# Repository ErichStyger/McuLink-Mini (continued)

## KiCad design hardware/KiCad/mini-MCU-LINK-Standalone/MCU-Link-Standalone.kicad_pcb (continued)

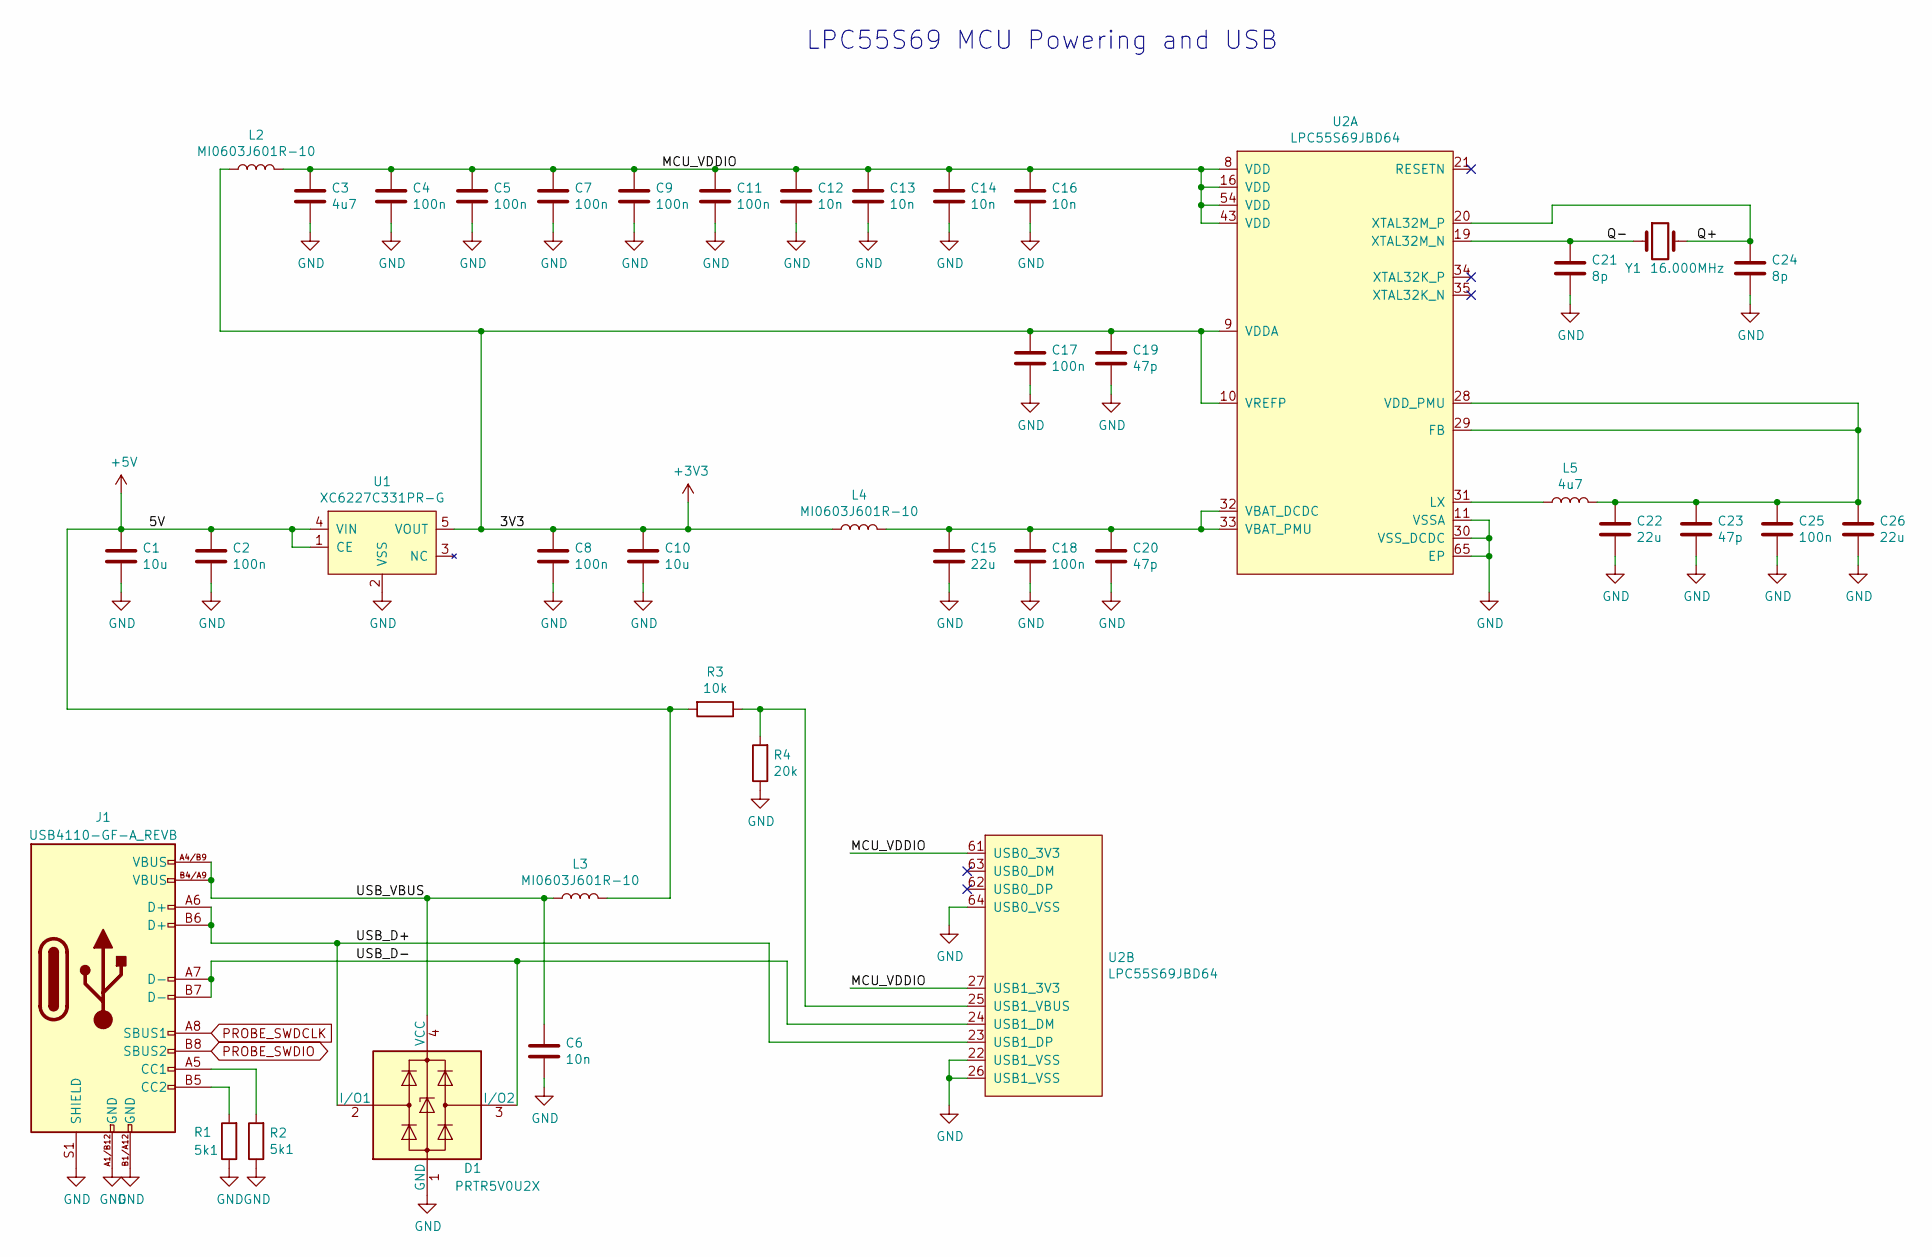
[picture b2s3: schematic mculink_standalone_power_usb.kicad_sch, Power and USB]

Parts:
C1, C10: 10u; C_0402_1005Metric
C2, C4, C5, C7, C8, C9, C11, C17, C18, C25: 100n; C_0402_1005Metric
C3: 4u7; C_0402_1005Metric
C6, C12, C13, C14, C16: 10n; C_0402_1005Metric
C15, C22, C26: 22u; C_0402_1005Metric
C19, C20, C23: 47p; C_0402_1005Metric
C21, C24: 8p; C_0402_1005Metric
D1: PRTR5V0U2X; SOT143B
J1: USB4110-GF-A_REVB; USB_C_Receptacle_GCT_USB4110-GF-A; PARTREV B
L2, L3, L4: MI0603J601R-10; L_0603_1608Metric
L5: 4u7; L_0603_1608Metric
R1, R2: 5k1; R_0402_1005Metric
R3: 10k; R_0402_1005Metric
R4: 20k; R_0402_1005Metric
U1: XC6227C331PR-G; SOT-89-5
U2: LPC55S69JBD64; LQFP-64-1EP_10x10mm_P0.5mm_EP5x5mm
Y1: 16.000MHz; CX3225GA16000D0PTVCC

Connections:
+3V3: C8.1, C10.1, C17.1, C19.1, L2.1, L4.1, U1.5 (VOUT), U2.9 (VDDA), U2.10 (VREFP); also elsewhere on the board
+5V: C1.1, C2.1, L3.2, R3.2, U1.1 (CE), U1.4 (VIN); also elsewhere on the board
/MCU-LINK Power and USB/MCU_VDDIO: C3.1, C4.1, C5.1, C7.1, C9.1, C11.1, C12.1, C13.1, C14.1, C16.1, L2.2, U2.8 (VDD), U2.16 (VDD), U2.27 (USB1_3V3), U2.43 (VDD), U2.54 (VDD), U2.61 (USB0_3V3)
/MCU-LINK Power and USB/Q+: C24.1, U2.20 (XTAL32M_P), Y1.2
/MCU-LINK Power and USB/Q-: C21.1, U2.19 (XTAL32M_N), Y1.1
/MCU-LINK Power and USB/USB_D+: D1.2 (I/O1), J1.A6 (D+), J1.B6 (D+), U2.23 (USB1_DP)
/MCU-LINK Power and USB/USB_D-: D1.3 (I/O2), J1.A7 (D-), J1.B7 (D-), U2.24 (USB1_DM)
/MCU-LINK Power and USB/USB_VBUS: C6.1, D1.4 (VCC), J1.A4/B9 (VBUS), J1.B4/A9 (VBUS), L3.1
GND: C1.2, C2.2, C3.2, C4.2, C5.2, C6.2, C7.2, C8.2, C9.2, C10.2, C11.2, C12.2, C13.2, C14.2, C15.2, C16.2, C17.2, C18.2, C19.2, C20.2, C21.2, C22.2, C23.2, C24.2, C25.2, C26.2, D1.1 (GND), J1.A1/B12 (GND), J1.B1/A12 (GND), J1.S1 (SHIELD), R1.1, R2.1, R4.1, U1.2 (VSS), U2.11 (VSSA), U2.22 (USB1_VSS), U2.26 (USB1_VSS), U2.30 (VSS_DCDC), U2.64 (USB0_VSS), U2.65 (EP); also elsewhere on the board
unnamed: J1.A5 (CC1), R2.2
unnamed: J1.B5 (CC2), R1.2
unnamed: C22.1, C23.1, C25.1, C26.1, L5.2, U2.28 (VDD_PMU), U2.29 (FB)
unnamed: L5.1, U2.31 (LX)
unnamed: C15.1, C18.1, C20.1, L4.2, U2.32 (VBAT_DCDC), U2.33 (VBAT_PMU)
unnamed: R3.1, R4.2, U2.25 (USB1_VBUS)
PROBE_SWDCLK: J1.A8 (SBUS1); also elsewhere on the board
PROBE_SWDIO: J1.B8 (SBUS2); also elsewhere on the board

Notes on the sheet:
LPC55S69 MCU Powering and USB

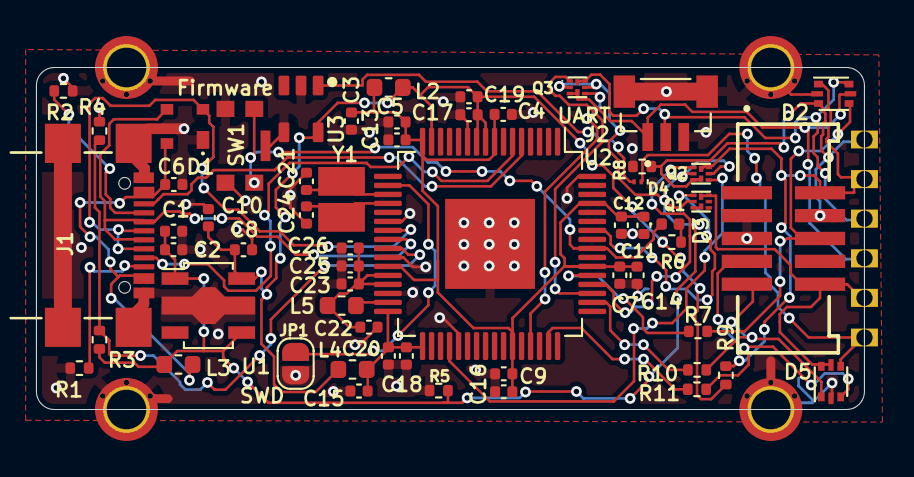
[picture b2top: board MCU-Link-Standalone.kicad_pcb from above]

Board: 2 copper layers, 46.0 x 19.0 mm, 69 parts (1 on the bottom side), 38 nets.

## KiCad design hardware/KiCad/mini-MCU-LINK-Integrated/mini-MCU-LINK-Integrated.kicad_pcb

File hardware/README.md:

# Outline
This folder contains hardware releated files and folders:
- Gerber: production files
- KiCad: KiCad project files for the standalone, intergrated and component version of the PCB

# Errata Rev v2.1
following resistors need to be removed
- R7, R6, R9 (100 Ohm resistor for UART Rx, Tx and SWCLK)

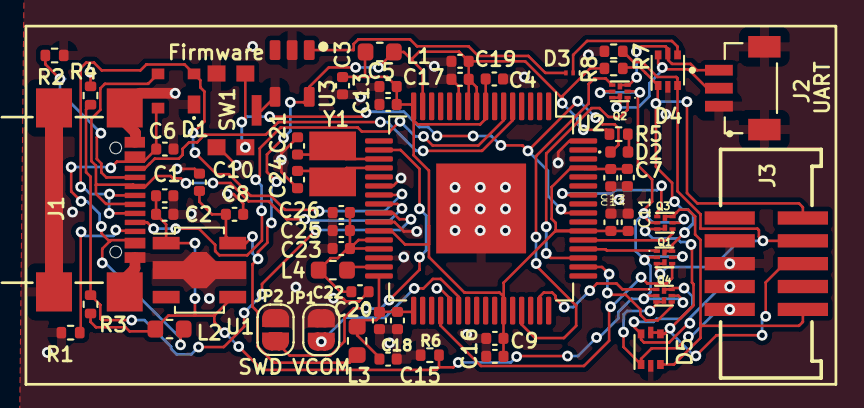
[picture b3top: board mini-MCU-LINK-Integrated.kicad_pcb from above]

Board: 2 copper layers, 57 parts (0 on the bottom side), 39 nets.

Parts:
C1, C10: 10u; C_0402_1005Metric
C2, C4, C5, C7, C8, C9, C11, C17, C18, C25: 100n; C_0402_1005Metric
C3: 4u7; C_0402_1005Metric
C6, C12, C13, C14, C16: 10n; C_0402_1005Metric
C15, C22, C26: 22u; C_0402_1005Metric
C19, C20, C23: 47p; C_0402_1005Metric
C21, C24: 8p; C_0402_1005Metric
D1: PRTR5V0U2X; SOT143B
D2: LED_RED; LED_0402_1005Metric
D3: PMEG3005AESFYL; Nexperia_DSN0603-2_0.6x0.3mm_P0.4mm
D4, D5: PESD5V0L5UV; SOT-666
J1: USB4110-GF-A_REVB; USB_C_Receptacle_GCT_USB4110-GF-A
J2: BM03B-SRSS-TB; JST_BM03B-SRSS-TB_LF__SN_
J3: Conn_02x05_Odd_Even; SWD_Pin_Header_Straight_2x05_Pitch1.27mm_SMD
JP1: VCOM disable; SolderJumper-2_P1.3mm_Open_RoundedPad1.0x1.5mm
JP2: SWD disable; SolderJumper-2_P1.3mm_Open_RoundedPad1.0x1.5mm
L1, L2, L3: MI0603J601R-10; L_0603_1608Metric
L4: 4u7; L_0603_1608Metric
Q1, Q2, Q3, Q4: PMDXB290UNE; SOT1216
R1, R2: 5k1; R_0402_1005Metric
R3, R6: 10k; R_0402_1005Metric
R4: 20k; R_0402_1005Metric
R5: 2k; R_0402_1005Metric
R7, R8: 100k; R_0402_1005Metric
SW1: KMR221GLFS; SW_C_K_KMR2
U1: XC6227C331PR-G; SOT-89-5
U2: LPC55S69JBD64; LQFP-64-1EP_10x10mm_P0.5mm_EP5x5mm
U3: STMPS2141STR; SOT95P280X145-5N
Y1: 16.000MHz; CX3225GA16000D0PTVCC

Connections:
+3V3: C8.1, C10.1, C17.1, C19.1, L1.1, L3.1, R5.1, R8.1, U1.5 (VOUT), U2.9 (VDDA), U2.10 (VREFP), U2.15 (PIO0_31), U3.5 (IN)
+5V: C1.1, C2.1, L2.2, Q1.2 (G), Q1.5 (G), Q2.2 (G), Q2.5 (G), Q3.2 (G), Q3.5 (G), Q4.2 (G), Q4.5 (G), R3.2, R6.1, U1.1 (CE), U1.4 (VIN)
/mini MCU-LINK Debug and UART interface/DETECT: Q4.4 (S), U2.50 (PIO0_22)
/mini MCU-LINK Debug and UART interface/ISP_CTRL: Q4.1 (S), U2.47 (PIO0_14)
/mini MCU-LINK Debug and UART interface/PIO0_5-ISP_EN-LED1_CTRL: D2.1 (K), SW1.1, SW1.3, U2.56 (PIO0_5)
/mini MCU-LINK Debug and UART interface/RESET: Q3.1 (S), U2.58 (PIO0_19)
/mini MCU-LINK Debug and UART interface/RXD: Q2.4 (S), U2.45 (PIO0_24)
/mini MCU-LINK Debug and UART interface/SWCLK: Q1.4 (S), U2.36 (PIO0_0)
/mini MCU-LINK Debug and UART interface/SWDIO: Q1.1 (S), U2.52 (PIO0_2)
/mini MCU-LINK Debug and UART interface/SWD_DISABLE: JP2.1 (A), U2.18 (PIO0_27)
/mini MCU-LINK Debug and UART interface/SWO: Q3.4 (S), U2.53 (PIO0_3)
/mini MCU-LINK Debug and UART interface/TARGET_DETECT: D5.1 (K1), J3.9, Q4.3 (D)
/mini MCU-LINK Debug and UART interface/TARGET_ISP_CTRL: D5.6 (K5), J3.7, Q4.6 (D)
/mini MCU-LINK Debug and UART interface/TARGET_RESET: D5.3 (K2), J3.10, Q3.6 (D)
/mini MCU-LINK Debug and UART interface/TARGET_RXD: D4.5 (K4), J2.1, Q2.3 (D)
/mini MCU-LINK Debug and UART interface/TARGET_SWCLK: D4.3 (K2), J3.4, Q1.3 (D), R7.1
/mini MCU-LINK Debug and UART interface/TARGET_SWDIO: D4.1 (K1), J3.2, Q1.6 (D), R8.2
/mini MCU-LINK Debug and UART interface/TARGET_SWO: D5.4 (K3), D5.5 (K4), J3.6, Q3.3 (D)
/mini MCU-LINK Debug and UART interface/TARGET_TXD: D4.6 (K5), J2.2, Q2.6 (D)
/mini MCU-LINK Debug and UART interface/TXD: Q2.1 (S), U2.51 (PIO0_25)
/mini MCU-LINK Debug and UART interface/VCC: D3.1 (K), D4.4 (K3)
/mini MCU-LINK Debug and UART interface/VCOM_DISABLE: JP1.1 (A), U2.38 (PIO0_18)
/mini MCU-LINK Power and USB/MCU_VDDIO: C3.1, C4.1, C5.1, C7.1, C9.1, C11.1, C12.1, C13.1, C14.1, C16.1, L1.2, U2.8 (VDD), U2.16 (VDD), U2.27 (USB1_3V3), U2.43 (VDD), U2.54 (VDD), U2.61 (USB0_3V3)
/mini MCU-LINK Power and USB/Q+: C24.1, U2.20 (XTAL32M_P), Y1.2
/mini MCU-LINK Power and USB/Q-: C21.1, U2.19 (XTAL32M_N), Y1.1
/mini MCU-LINK Power and USB/USB_D+: D1.2 (I/O1), J1.A6 (D+), J1.B6 (D+), U2.23 (USB1_DP)
/mini MCU-LINK Power and USB/USB_D-: D1.3 (I/O2), J1.A7 (D-), J1.B7 (D-), U2.24 (USB1_DM)
/mini MCU-LINK Power and USB/USB_VBUS: C6.1, D1.4 (VCC), J1.A4/B9 (VBUS), J1.B4/A9 (VBUS), L2.1
GND: C1.2, C2.2, C3.2, C4.2, C5.2, C6.2, C7.2, C8.2, C9.2, C10.2, C11.2, C12.2, C13.2, C14.2, C15.2, C16.2, C17.2, C18.2, C19.2, C20.2, C21.2, C22.2, C23.2, C24.2, C25.2, C26.2, D1.1 (GND), D4.2 (A), D5.2 (A), J1.A1/B12 (GND), J1.B1/A12 (GND), J1.S1 (SHIELD), J2.3, J2.S1 (SHIELD), J2.S2 (SHIELD__1), J3.3, J3.5, JP1.2 (B), JP2.2 (B), R1.1, R2.1, R4.1, R6.2, R7.2, SW1.2, SW1.4, SW1.5 (SHIELD), U1.2 (VSS), U2.11 (VSSA), U2.22 (USB1_VSS), U2.26 (USB1_VSS), U2.30 (VSS_DCDC), U2.37 (PIO0_9), U2.64 (USB0_VSS), U2.65 (EP), U3.2 (GND), U3.4 (EN)
unnamed: D2.2 (A), R5.2
unnamed: D3.2 (A), U3.1 (OUT)
unnamed: J1.A5 (CC1), R2.2
unnamed: J1.B5 (CC2), R1.2
unnamed: C22.1, C23.1, C25.1, C26.1, L4.2, U2.28 (VDD_PMU), U2.29 (FB)
unnamed: L4.1, U2.31 (LX)
unnamed: C15.1, C18.1, C20.1, L3.2, U2.32 (VBAT_DCDC), U2.33 (VBAT_PMU)
unnamed: R3.1, R4.2, U2.25 (USB1_VBUS)
PROBE_SWDCLK: J1.A8 (SBUS1), U2.6 (PIO0_11)
PROBE_SWDIO: J1.B8 (SBUS2), U2.5 (PIO0_12)

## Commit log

2024-02-01 initial version, from PAIND of Dario Scheuber
2024-02-01 updated documentation
2024-02-01 no message
2024-02-01 added bottom image
2024-02-01 updated information
2024-02-05 added errata
2024-02-05 fixed some DRC errors and warnings
2024-02-05 added gitignore
2024-02-06 added notes, updated 3D model
2024-03-11 added initial drone version (work in progress)
2024-03-12 updated schematic part
2024-03-12 cleanup and ERC fixes
2024-03-12 made it warning free with KiCAD 8
2024-03-22 added new project for Drone
2024-03-22 updated with drone project files
2024-03-22 adding data sheets
2024-03-22 updated BOM
2024-03-22 cleanup
2024-03-22 worked on layout
2024-03-22 fixed warnings
2024-03-24 added 3D models
2024-03-24 improved layout
2024-03-25 optimized layout
2024-03-25 optimized traces
2024-03-26 added JST-GH for UART
2024-03-27 production files for V0.1
2024-03-27 fixed silkscreen
2024-04-12 updated schematics
2024-04-23 updated parts and minor tweaks
2024-04-29 moved files
2024-04-29 consolidated notes
2024-04-29 added enclosure
2024-05-01 sent v0.2 to PCB production
